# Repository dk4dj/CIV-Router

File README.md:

Router für den Icom CI-V Bus von DJ0ABR
siehe: https://projects.dj0abr.de/doku.php?id=de:civrouter:civ_overview

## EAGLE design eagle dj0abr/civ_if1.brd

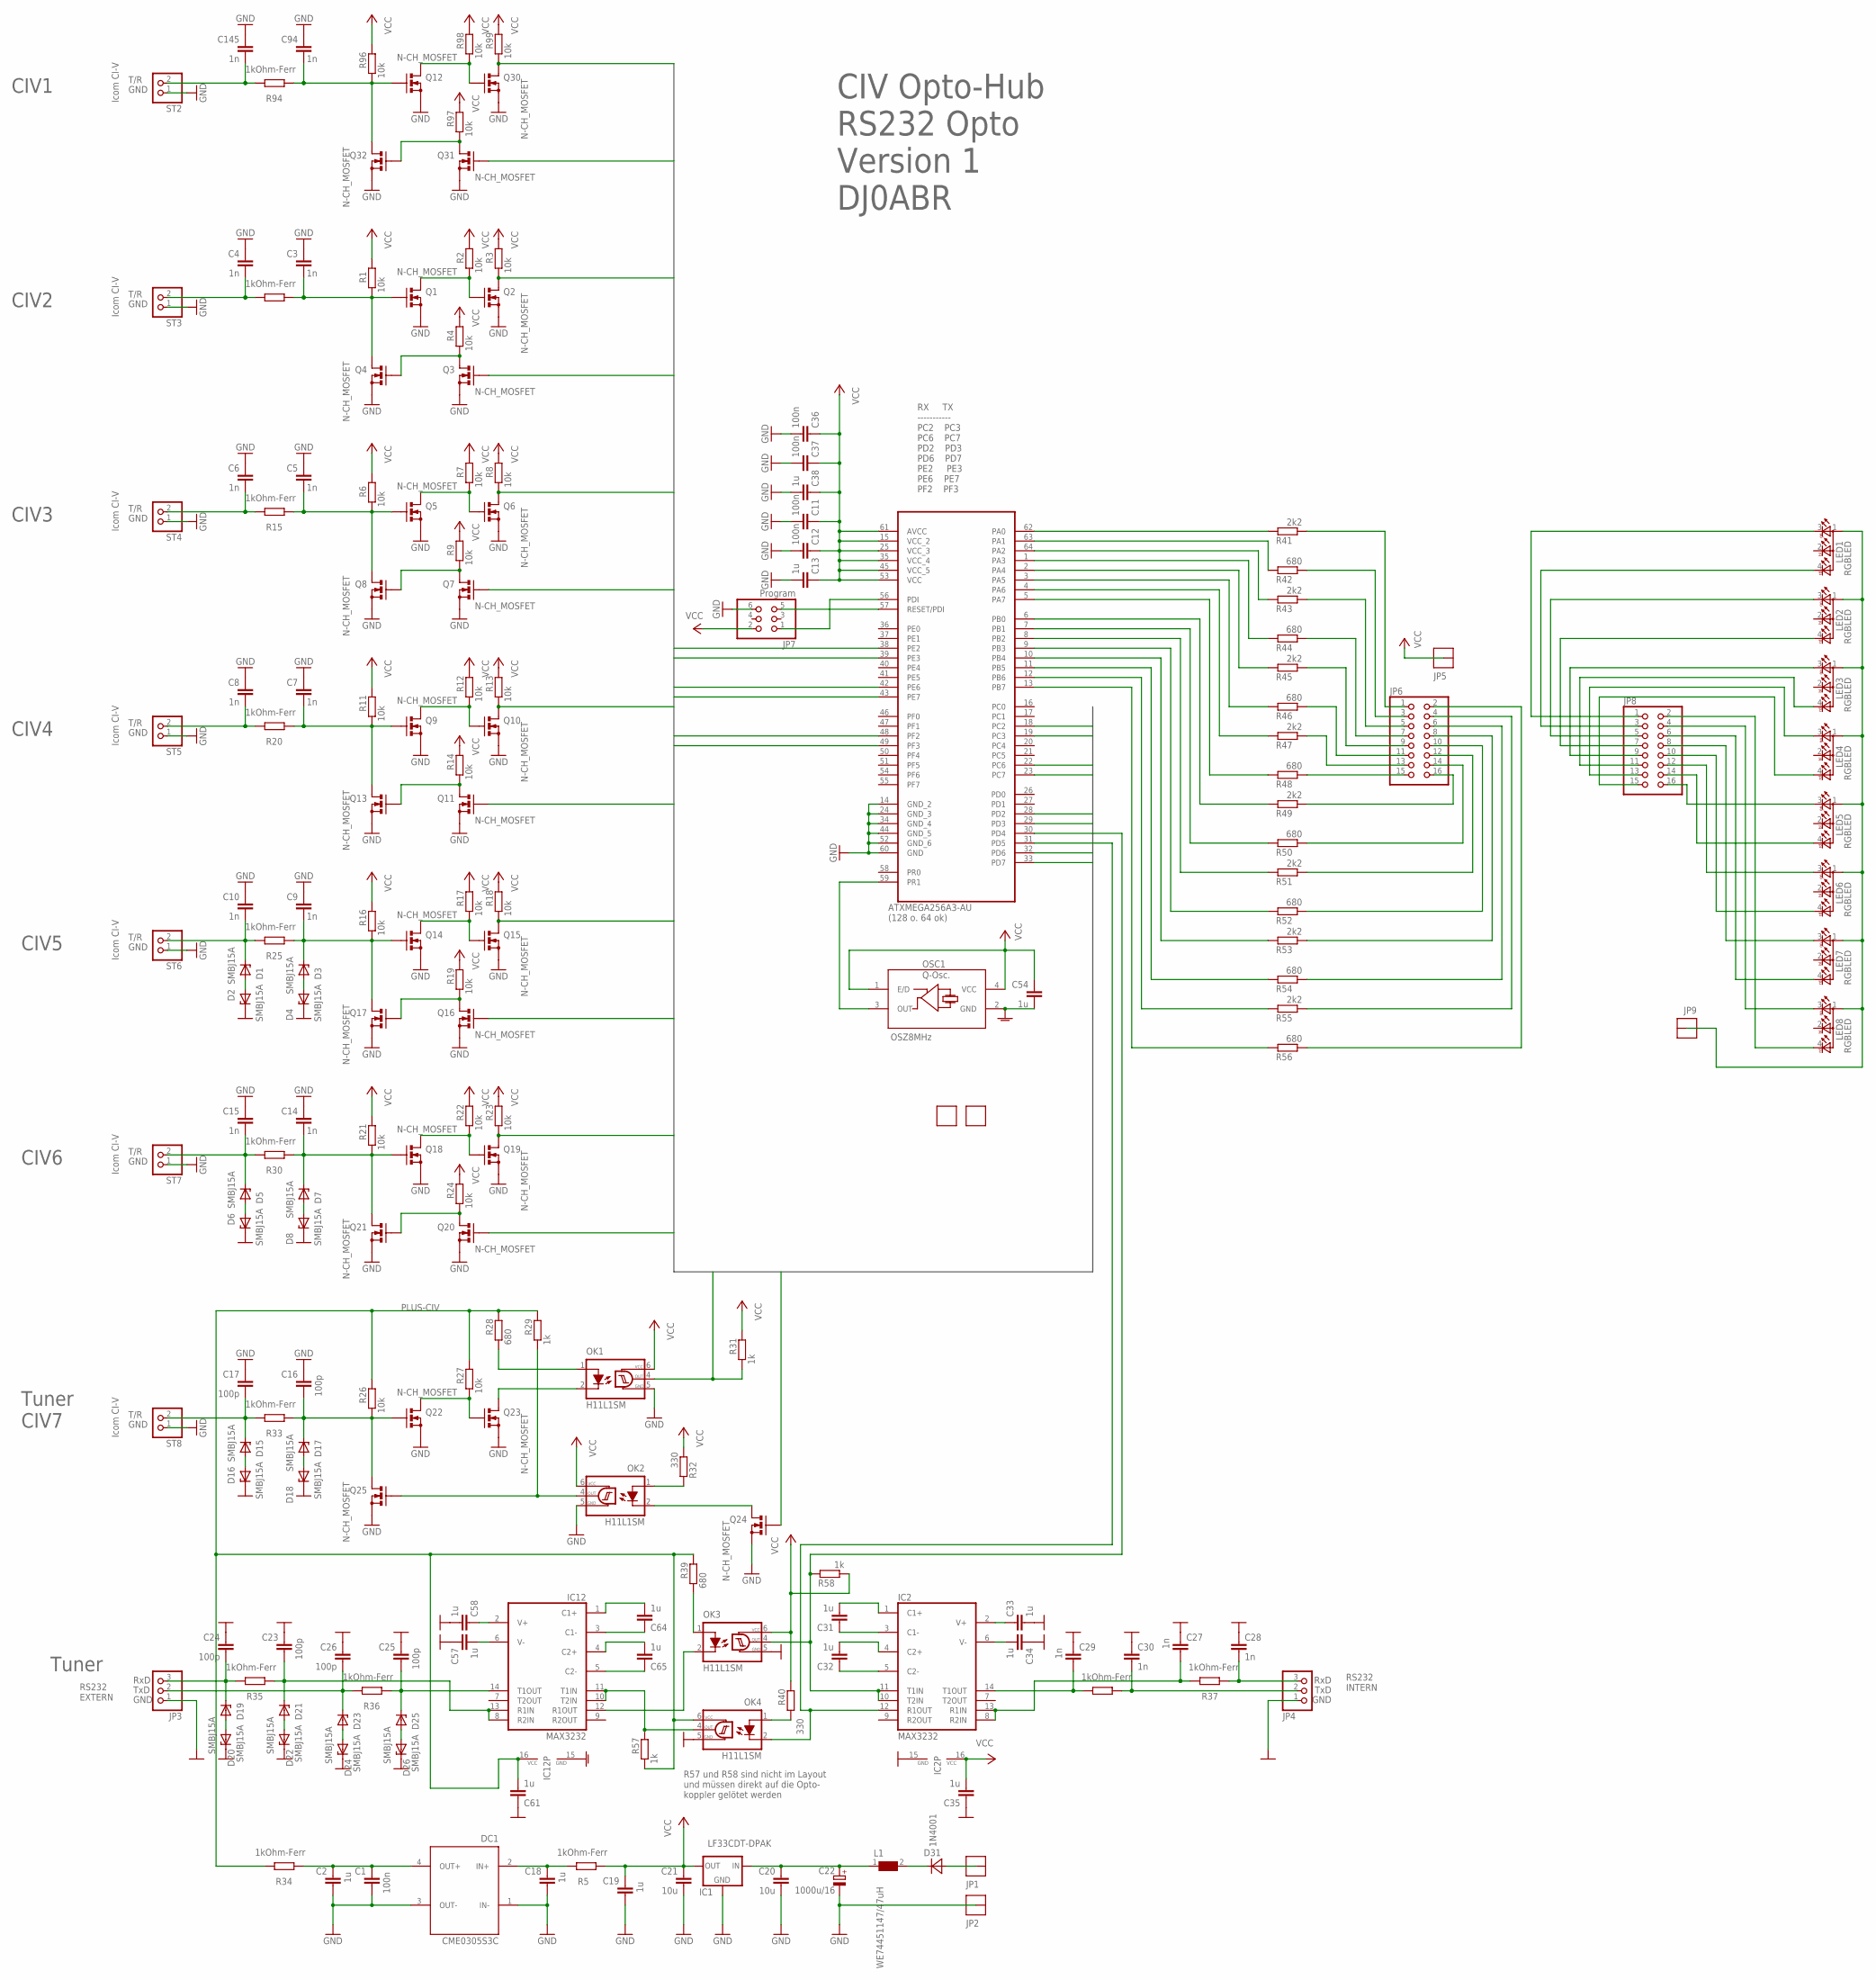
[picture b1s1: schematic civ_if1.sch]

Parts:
C1, C11, C12, C36, C37: 100n; C0603
C2, C13, C18, C19, C35, C38, C61: 1u; C0603
C3, C4, C5, C6, C7, C8, C9, C10, C14, C15, C27, C28, C29, C30, C94, C145: 1n; C0603
C16, C17, C23, C24, C25, C26: 100p; C0603
C20: 10u; C0805
C21: 10u; C0603
C22: 1000u/16; E5-13
C31, C32, C33, C34, C54, C57, C58, C64, C65: 1u; C0603K
D1, D2, D3, D4, D5, D6, D7, D8, D15, D16, D17, D18, D19, D20, D21, D22, D23, D24, D25, D26: SMBJ15A; SMA
D31: 1N4001; MELF
DC1: CME0305S3C; MURATA_DCDC
FID1, FID2: FIDUCIAL
IC1: LF33CDT-DPAK; DPACK
IC2, IC12: MAX3232; SO16
JP1, JP2, JP5, JP9: THICKPINSQUARE; THICKPIN
JP3, JP4: PINHD-1X3; 1X03
JP6, JP8: PINHD-2X8; 2X08
JP7: Program; 2X03
L1: WE74451147/47uH; S
LED1, LED2, LED3, LED4, LED5, LED6, LED7, LED8: RGBLED; PLCC4_WE_LED
OK1, OK2, OK3, OK4: H11L1SM; DIL6-SMD
OSC1: OSZ8MHz; QOSC_AQO7015
Q1, Q2, Q3, Q4, Q5, Q6, Q7, Q8, Q9, Q10, Q11, Q12, Q13, Q14, Q15, Q16, Q17, Q18, Q19, Q20, Q21, Q22, Q23, Q24, Q25, Q30, Q31, Q32: N-CH_MOSFET; SOT23
R1, R2, R3, R4, R6, R7, R8, R9, R11, R12, R13, R14, R16, R17, R18, R19, R21, R22, R23, R24, R26, R27, R96, R97, R98, R99: 10k; R0603
R5, R10, R15, R20, R25, R30, R33, R34, R35, R36, R37, R38, R94: 1kOhm-Ferr; R0603
R28, R39, R42, R44, R46, R48, R50, R52, R54, R56: 680; R0603
R29, R31, R57, R58: 1k; R0603
R32, R40: 330; R0603
R41, R43, R45, R47, R49, R51, R53, R55: 2k2; R0603
ST2, ST3, ST4, ST5, ST6, ST7, ST8: PINHEAD2X1SMALL; PINHEAD1X2
U1: ATXMEGA256A3-AU; QFP80P1600X1600X120-64N

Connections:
GND: C1.2, C2.2, C3.1, C4.1, C5.1, C6.1, C7.1, C8.1, C9.1, C10.1, C11.2, C12.2, C13.2, C14.1, C15.1, C16.1, C17.1, C18.2, C19.2, C20.2, C21.2, C22.-, C23.1, C24.1, C25.1, C26.1, C27.1, C28.1, C29.1, C30.1, C33.2, C34.1, C35.1, C36.2, C37.2, C38.2, C54.2, C57.1, C58.2, C61.1, C94.1, C145.1, D2.C, D4.C, D6.C, D8.C, D16.C, D18.C, D20.C, D22.C, D24.C, D26.C, DC1.1 (IN-), DC1.3 (OUT-), IC1.4 (GND), IC2.15 (GND), IC12.15 (GND), JP2.1, JP3.1, JP4.1, JP7.6, OK1.5 (GND), OK2.5 (GND), OK3.5 (GND), OK4.5 (GND), OSC1.2 (GND), Q1.2 (S), Q2.2 (S), Q3.2 (S), Q4.2 (S), Q5.2 (S), Q6.2 (S), Q7.2 (S), Q8.2 (S), Q9.2 (S), Q10.2 (S), Q11.2 (S), Q12.2 (S), Q13.2 (S), Q14.2 (S), Q15.2 (S), Q16.2 (S), Q17.2 (S), Q18.2 (S), Q19.2 (S), Q20.2 (S), Q21.2 (S), Q22.2 (S), Q23.2 (S), Q24.2 (S), Q25.2 (S), Q30.2 (S), Q31.2 (S), Q32.2 (S), ST2.1, ST3.1, ST4.1, ST5.1, ST6.1, ST7.1, ST8.1, U1.14 (GND_2), U1.24 (GND_3), U1.34 (GND_4), U1.44 (GND_5), U1.52 (GND_6), U1.60 (GND)
unnamed: OK1.2 (C), Q23.3 (D)
unnamed: Q1.3 (D), Q2.1 (G), R2.1
unnamed: OSC1.3 (OUT), U1.59 (PR1)
unnamed: C1.1, C2.1, DC1.4 (OUT+), R34.2
unnamed: Q3.3 (D), Q4.1 (G), R4.1
unnamed: C18.1, DC1.2 (IN+), R5.1
unnamed: C4.2, R10.1, ST3.2
unnamed: OK2.1 (A), R32.2
unnamed: Q5.3 (D), Q6.1 (G), R7.1
unnamed: C94.2, Q12.1 (G), Q32.3 (D), R94.2, R96.1
unnamed: C3.2, Q1.1 (G), Q4.3 (D), R1.1, R10.2
unnamed: Q7.3 (D), Q8.1 (G), R9.1
unnamed: C6.2, R15.1, ST4.2
unnamed: C5.2, Q5.1 (G), Q8.3 (D), R6.1, R15.2
unnamed: C8.2, R20.1, ST5.2
unnamed: Q9.3 (D), Q10.1 (G), R12.1
unnamed: Q22.3 (D), Q23.1 (G), R27.1
unnamed: OK2.4 (OUT), Q25.1 (G), R29.1
unnamed: Q11.3 (D), Q13.1 (G), R14.1
unnamed: C20.1, C22.+, IC1.1 (IN), L1.1
unnamed: C7.2, Q9.1 (G), Q13.3 (D), R11.1, R20.2
unnamed: C10.2, D1.C, R25.1, ST6.2
unnamed: Q14.3 (D), Q15.1 (G), R17.1
unnamed: C9.2, D3.C, Q14.1 (G), Q17.3 (D), R16.1, R25.2
unnamed: C15.2, D5.C, R30.1, ST7.2
unnamed: Q16.3 (D), Q17.1 (G), R19.1
unnamed: JP6.1, R41.1
unnamed: C14.2, D7.C, Q18.1 (G), Q21.3 (D), R21.1, R30.2
unnamed: C17.2, D15.C, R33.1, ST8.2
unnamed: Q18.3 (D), Q19.1 (G), R22.1
unnamed: C16.2, D17.C, Q22.1 (G), Q25.3 (D), R26.1, R33.2
unnamed: JP6.3, R42.1
unnamed: Q20.3 (D), Q21.1 (G), R24.1
unnamed: D31.2 (A), JP1.1
unnamed: D15.A, D16.A
unnamed: D17.A, D18.A
unnamed: C24.2, D19.C, JP3.3, R35.1
unnamed: C23.2, D21.C, IC12.8 (R2IN), IC12.13 (R1IN), R35.2
unnamed: D19.A, D20.A
unnamed: D21.A, D22.A
unnamed: C26.2, D23.C, JP3.2, R36.1
unnamed: C28.2, JP4.3, R37.1
unnamed: D23.A, D24.A
unnamed: D25.A, D26.A
unnamed: C64.1, IC12.3 (C1-)
unnamed: C64.2, IC12.1 (C1+)
unnamed: C65.2, IC12.4 (C2+)
unnamed: C65.1, IC12.5 (C2-)
unnamed: C58.1, IC12.2 (V+)
unnamed: C57.2, IC12.6 (V-)
unnamed: IC12.10 (T2IN), IC12.11 (T1IN), OK4.4 (OUT), R57.2
unnamed: IC12.12 (R1OUT), OK3.2 (C)
unnamed: C27.2, IC2.8 (R2IN), IC2.13 (R1IN), R37.2
unnamed: C25.2, D25.C, IC12.14 (T1OUT), R36.2
unnamed: JP6.5, R43.1
unnamed: JP6.7, R44.1
unnamed: C30.2, JP4.2, R38.1
unnamed: JP6.9, R45.1
unnamed: JP6.11, R46.1
unnamed: C31.1, IC2.3 (C1-)
unnamed: C31.2, IC2.1 (C1+)
unnamed: C32.2, IC2.4 (C2+)
unnamed: C32.1, IC2.5 (C2-)
unnamed: C33.1, IC2.2 (V+)
unnamed: C34.2, IC2.6 (V-)
unnamed: IC2.10 (T2IN), IC2.11 (T1IN), OK3.4 (OUT), R58.2, U1.30 (PD4)
unnamed: IC2.12 (R1OUT), OK4.2 (C), U1.31 (PD5)
unnamed: C29.2, IC2.14 (T1OUT), R38.2
unnamed: JP6.13, R47.1
unnamed: OK3.1 (A), R39.1
unnamed: OK4.1 (A), R40.1
unnamed: JP6.15, R48.1
unnamed: JP6.16, R49.1
unnamed: JP6.14, R50.1
unnamed: JP6.12, R51.1
unnamed: JP6.10, R52.1
unnamed: JP6.8, R53.1
unnamed: JP6.6, R54.1
unnamed: JP6.4, R55.1
unnamed: JP6.2, R56.1
unnamed: R41.2, U1.62 (PA0)
unnamed: R42.2, U1.63 (PA1)
unnamed: R43.2, U1.64 (PA2)
unnamed: R44.2, U1.1 (PA3)
unnamed: R45.2, U1.2 (PA4)
unnamed: R46.2, U1.3 (PA5)
unnamed: R47.2, U1.4 (PA6)
unnamed: R48.2, U1.5 (PA7)
unnamed: R49.2, U1.6 (PB0)
unnamed: R50.2, U1.7 (PB1)
unnamed: R51.2, U1.8 (PB2)
unnamed: R52.2, U1.9 (PB3)
unnamed: R53.2, U1.10 (PB4)
unnamed: R54.2, U1.11 (PB5)
unnamed: D31.1 (C), L1.2
unnamed: R55.2, U1.12 (PB6)
unnamed: R56.2, U1.13 (PB7)
unnamed: D1.A, D2.A
unnamed: Q12.3 (D), Q30.1 (G), R98.1
unnamed: JP7.5, U1.57 (RESET/PDI)
unnamed: JP7.1, U1.56 (PDI)
unnamed: D3.A, D4.A
unnamed: D5.A, D6.A
unnamed: D7.A, D8.A
unnamed: Q31.3 (D), Q32.1 (G), R97.1
unnamed: C145.2, R94.1, ST2.2
unnamed: OK2.2 (C), Q24.3 (D)
unnamed: JP9.1, LED1.1 (A2), LED2.1 (A2), LED3.1 (A2), LED4.1 (A2), LED5.1 (A2), LED6.1 (A2), LED7.1 (A2), LED8.1 (A2)
unnamed: JP8.1, LED1.3 (CRED)
unnamed: JP8.3, LED1.4 (CGREEN)
unnamed: JP8.5, LED2.3 (CRED)
unnamed: JP8.7, LED2.4 (CGREEN)
unnamed: JP8.9, LED3.3 (CRED)
unnamed: JP8.11, LED3.4 (CGREEN)
unnamed: JP8.13, LED4.3 (CRED)
unnamed: JP8.15, LED4.4 (CGREEN)
unnamed: JP8.16, LED5.3 (CRED)
unnamed: JP8.14, LED5.4 (CGREEN)
unnamed: JP8.12, LED6.3 (CRED)
unnamed: JP8.10, LED6.4 (CGREEN)
unnamed: JP8.8, LED7.3 (CRED)
unnamed: JP8.6, LED7.4 (CGREEN)
unnamed: JP8.4, LED8.3 (CRED)
unnamed: JP8.2, LED8.4 (CGREEN)
PLUS-CIV: C61.2, IC12.16 (VCC), OK4.6 (VCC), R26.2, R27.2, R28.2, R29.2, R34.1, R39.2, R57.1
UART1: Q30.3 (D), R99.1, U1.18 (PC2)
UART2: Q31.1 (G), U1.19 (PC3)
UART3: Q2.3 (D), R3.1, U1.22 (PC6)
UART4: Q3.1 (G), U1.23 (PC7)
UART5: Q6.3 (D), R8.1, U1.28 (PD2)
UART6: Q7.1 (G), U1.29 (PD3)
UART7: Q10.3 (D), R13.1, U1.32 (PD6)
UART8: Q11.1 (G), U1.33 (PD7)
UART9: Q15.3 (D), R18.1, U1.38 (PE2)
UART10: Q16.1 (G), U1.39 (PE3)
UART11: Q19.3 (D), R23.1, U1.42 (PE6)
UART12: Q20.1 (G), U1.43 (PE7)
UART13: OK1.4 (OUT), R31.1, U1.48 (PF2)
UART14: Q24.1 (G), U1.49 (PF3)
UART15: OK1.1 (A), R28.1
VCC: C11.1, C12.1, C13.1, C19.1, C21.1, C35.2, C36.1, C37.1, C38.1, C54.1, IC1.3 (OUT), IC2.16 (VCC), JP5.1, JP7.2, OK1.6 (VCC), OK2.6 (VCC), OK3.6 (VCC), OSC1.1 (E/D), OSC1.4 (VCC), R1.2, R2.2, R3.2, R4.2, R5.2, R6.2, R7.2, R8.2, R9.2, R11.2, R12.2, R13.2, R14.2, R16.2, R17.2, R18.2, R19.2, R21.2, R22.2, R23.2, R24.2, R31.2, R32.1, R40.2, R58.1, R96.2, R97.2, R98.2, R99.2, U1.15 (VCC_2), U1.25 (VCC_3), U1.35 (VCC_4), U1.45 (VCC_5), U1.53 (VCC), U1.61 (AVCC)

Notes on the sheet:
T/R
GND
Icom CI-V
RX TX ----------- PC2 PC3 PC6 PC7 PD2 PD3 PD6 PD7 PE2 PE3 PE6 PE7 PF2 PF3
ATXMEGA256A3-AU (128 o. 64 ok)
CIV Opto-Hub RS232 Opto Version 1 DJ0ABR
Tuner CIV7
CIV1
CIV2
CIV3
CIV4
CIV5
CIV6
TxD
RxD
RS232 EXTERN
RS232 INTERN
Tuner
R57 und R58 sind nicht im Layout und müssen direkt auf die Opto- koppler gelötet werden

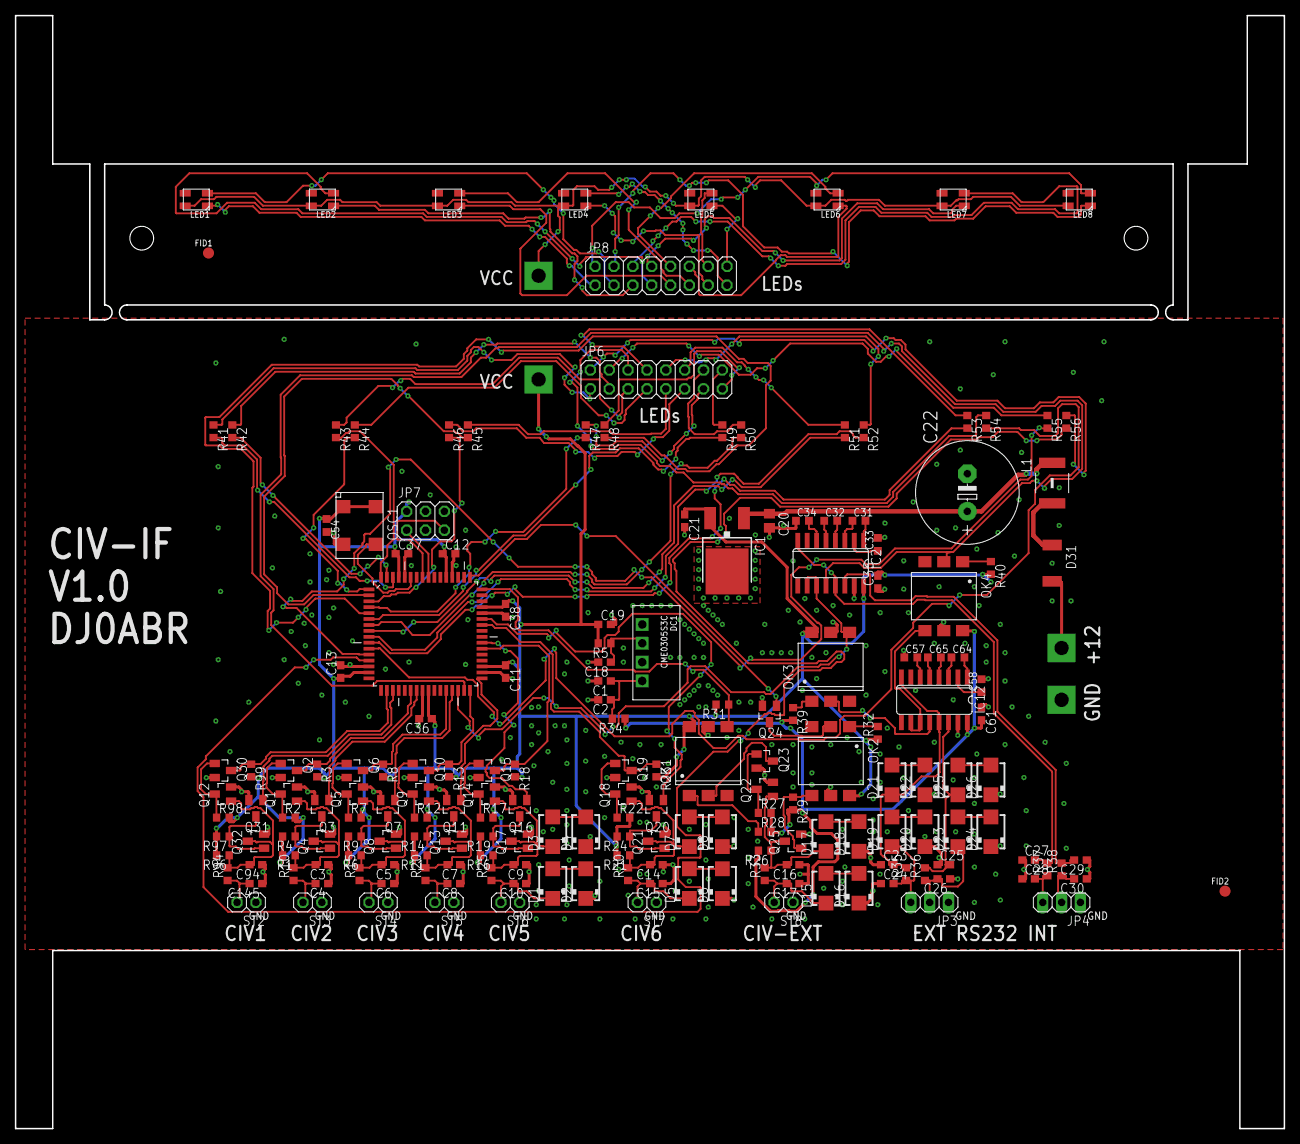
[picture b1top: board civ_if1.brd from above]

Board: 2 copper layers, 171.0 x 150.0 mm, 193 parts (0 on the bottom side), 142 nets.

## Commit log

2025-04-06 Create firmware
2025-04-06 Add files via upload
    initial release of DJ0ABR
